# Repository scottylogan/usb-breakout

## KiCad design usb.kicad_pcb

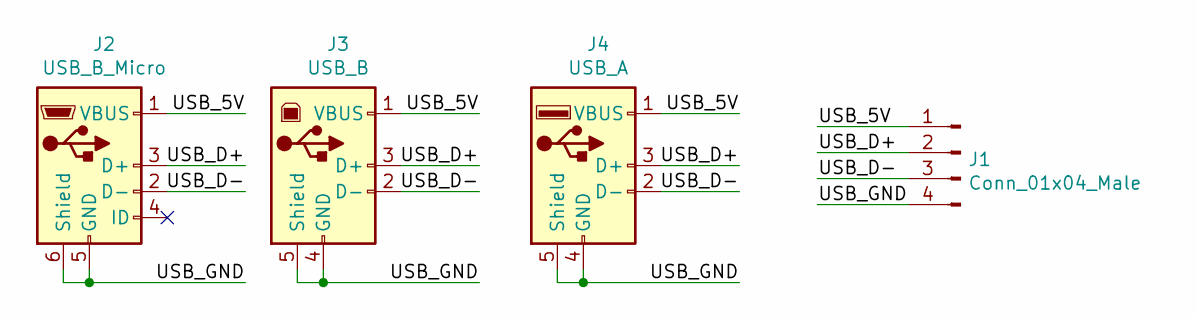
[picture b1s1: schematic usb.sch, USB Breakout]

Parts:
J1: Conn_01x04_Male; PinHeader_1x04_P2.54mm_Vertical
J2: USB_B_Micro; USB_Micro-B_Wuerth_614105150721_Vertical
J3: USB_B; USB_B_Lumberg_2411_02_Horizontal
J4: USB_A; USB_A_Molex_67643_Horizontal

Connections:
/USB_5V: J1.1, J2.1 (VBUS), J3.1 (VBUS), J4.1 (VBUS)
/USB_D+: J1.2, J2.3 (D+), J3.3 (D+), J4.3 (D+)
/USB_D-: J1.3, J2.2 (D-), J3.2 (D-), J4.2 (D-)
/USB_GND: J1.4, J2.5 (GND), J2.6 (Shield), J3.4 (GND), J3.5 (Shield), J4.4 (GND), J4.5 (Shield)

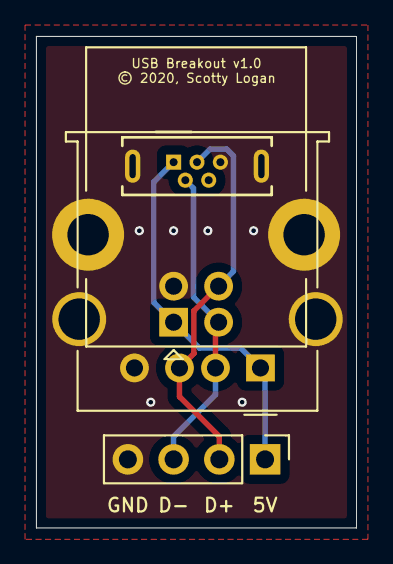
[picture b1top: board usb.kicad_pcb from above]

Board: 2 copper layers, 17.8 x 27.3 mm, 4 parts (0 on the bottom side), 4 nets.

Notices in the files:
usb.kicad_pcb:
© 2020, Scotty Logan
